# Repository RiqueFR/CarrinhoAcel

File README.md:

# CarrinhoAcel

Este projeto consiste no projeto de um robô/carrinho controlado remotamente por meio de comunicação Bluetooth e os dados lidos de um acelorômetro, que foi preso a uma luva sendo assim responsável por direcionar o robô conforme a inclinação da mão do condutor.</br>
O projeto foi desenvolvido para a disciplina de Projeto Integrado de Computação, no segundo período do curso de Engenharia de Computação da UFES.

## Esquemático

No diretório "Esq_Eagle" é possível encontrar o esquemático eletrônico desenvolvido tanto para a luva quanto para o carrinho, em seus respectivos diretórios.

## Funcionamento

O projeto funciona basicamente da seguinte forma, um Arduíno lê os dados do sensor de acelerômetro, transforma esses dados em uma direção, representada por um caractér, e um valor entre 0 e 1, que representa o quão inclinada está a luva.
Esses dado são passados via Bluetooth para outro Arduíno que está no robô, e ele controla a velocidade dos motores de acordo com a direção e o decimal recebido, que representa uma porcentagem da velocidade dele.

## Outros

É possível ver mais informações do projeto no documento "Henrique_Thiago_Henrique.pdf", que foi o arquivo enviado como relatório para o professor da disciplina.

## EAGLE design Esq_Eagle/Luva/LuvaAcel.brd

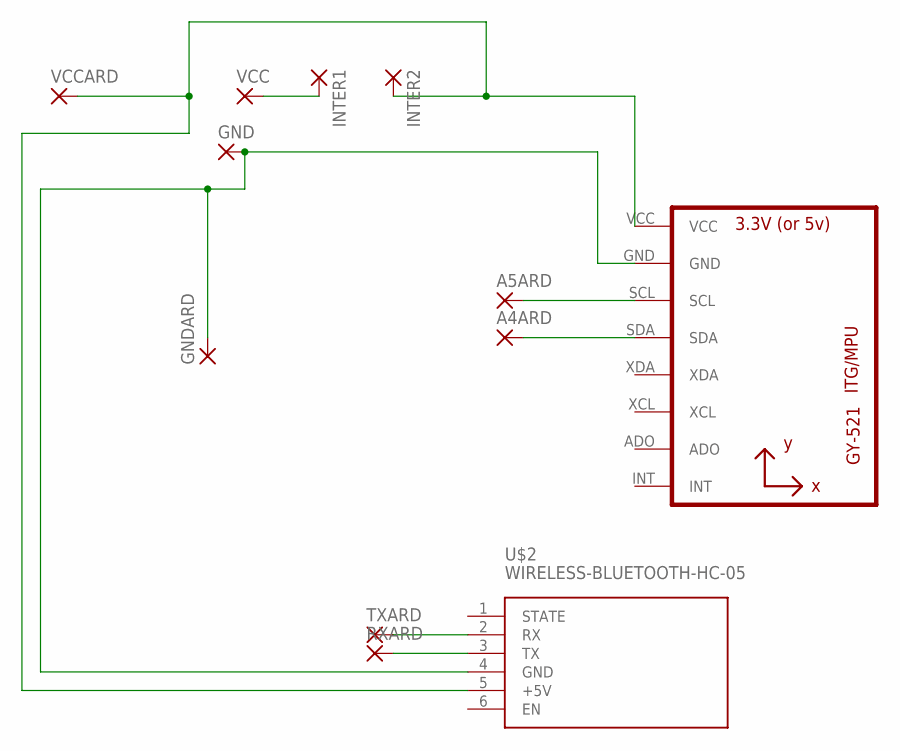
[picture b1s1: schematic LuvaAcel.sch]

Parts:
A4ARD, A5ARD: 3,17/1,1
GND: 3,17/1,1
GNDARD: 3,17/1,1
INTER1, INTER2: 3,17/1,1
RXARD: 3,17/1,1
TXARD: 3,17/1,1
U1: GY-521MPU6050; GY-521
U$2: WIRELESS-BLUETOOTH-HC-05
VCC: 3,17/1,1
VCCARD: 3,17/1,1

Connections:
unnamed: A5ARD.1, U1.SCL
unnamed: A4ARD.1, U1.SDA
unnamed: GND.1, GNDARD.1, U1.GND, U$2.4 (GND)
unnamed: TXARD.1, U$2.2 (RX)
unnamed: RXARD.1, U$2.3 (TX)
unnamed: INTER2.1, U1.VCC, U$2.5 (+5V), VCCARD.1
unnamed: INTER1.1, VCC.1

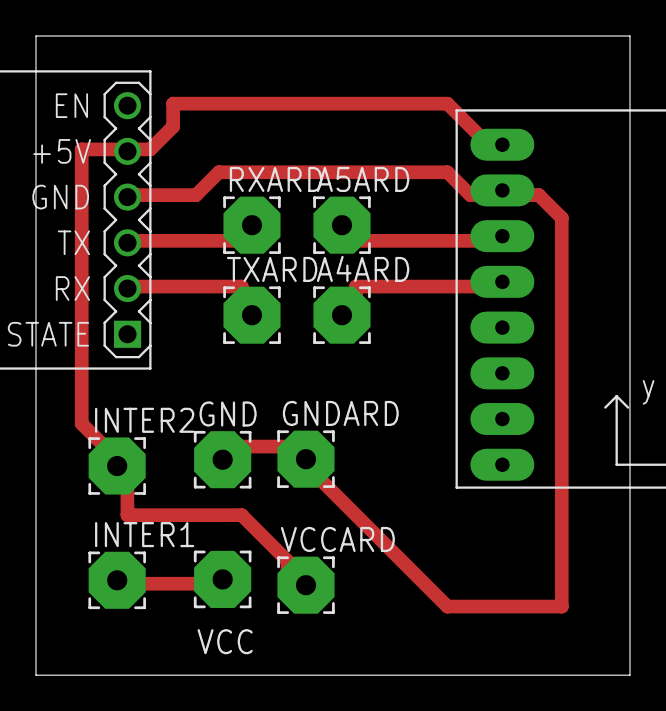
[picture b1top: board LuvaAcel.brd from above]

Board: 2 copper layers, 33.0 x 35.5 mm, 12 parts (0 on the bottom side), 7 nets.

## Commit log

2019-10-08 Adicionado código simples para luva
2019-10-15 CodCarrinho
    cadfas
2019-10-15 Arrumado codigo luva + adicionado comunicacao
2019-10-17 Modificando arquivo CodCarrinho para CodCarrinho.ino e movendo ele para sua pasta
2019-10-17 Modificado os codigos
2019-10-17 Update 17/10-Inserida comunicação do carrinho.
2019-10-24 Codigo quase funcionando
2019-10-24 codigo quase pronto
2019-10-24 codigo quase pronto2
2019-10-24 Funcionando, precisad
2019-10-29 Adicionando esquematico
2019-10-29 Removendo os esquematicos antigos
2019-10-31 Adicionando codigo para RGB
2019-11-06 Testado
2019-11-12 gerando arquivo para impressao das placas
2019-12-04 Novo codigo carrinho
2020-06-21 Formataçao melhor do codigo e excluindo arquivos nao utilizados

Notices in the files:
parts and their libraries:
diy-modules: Released under the Creative Commons Attribution 4.0 International License: http://creativecommons.org/licenses/by/4.0
